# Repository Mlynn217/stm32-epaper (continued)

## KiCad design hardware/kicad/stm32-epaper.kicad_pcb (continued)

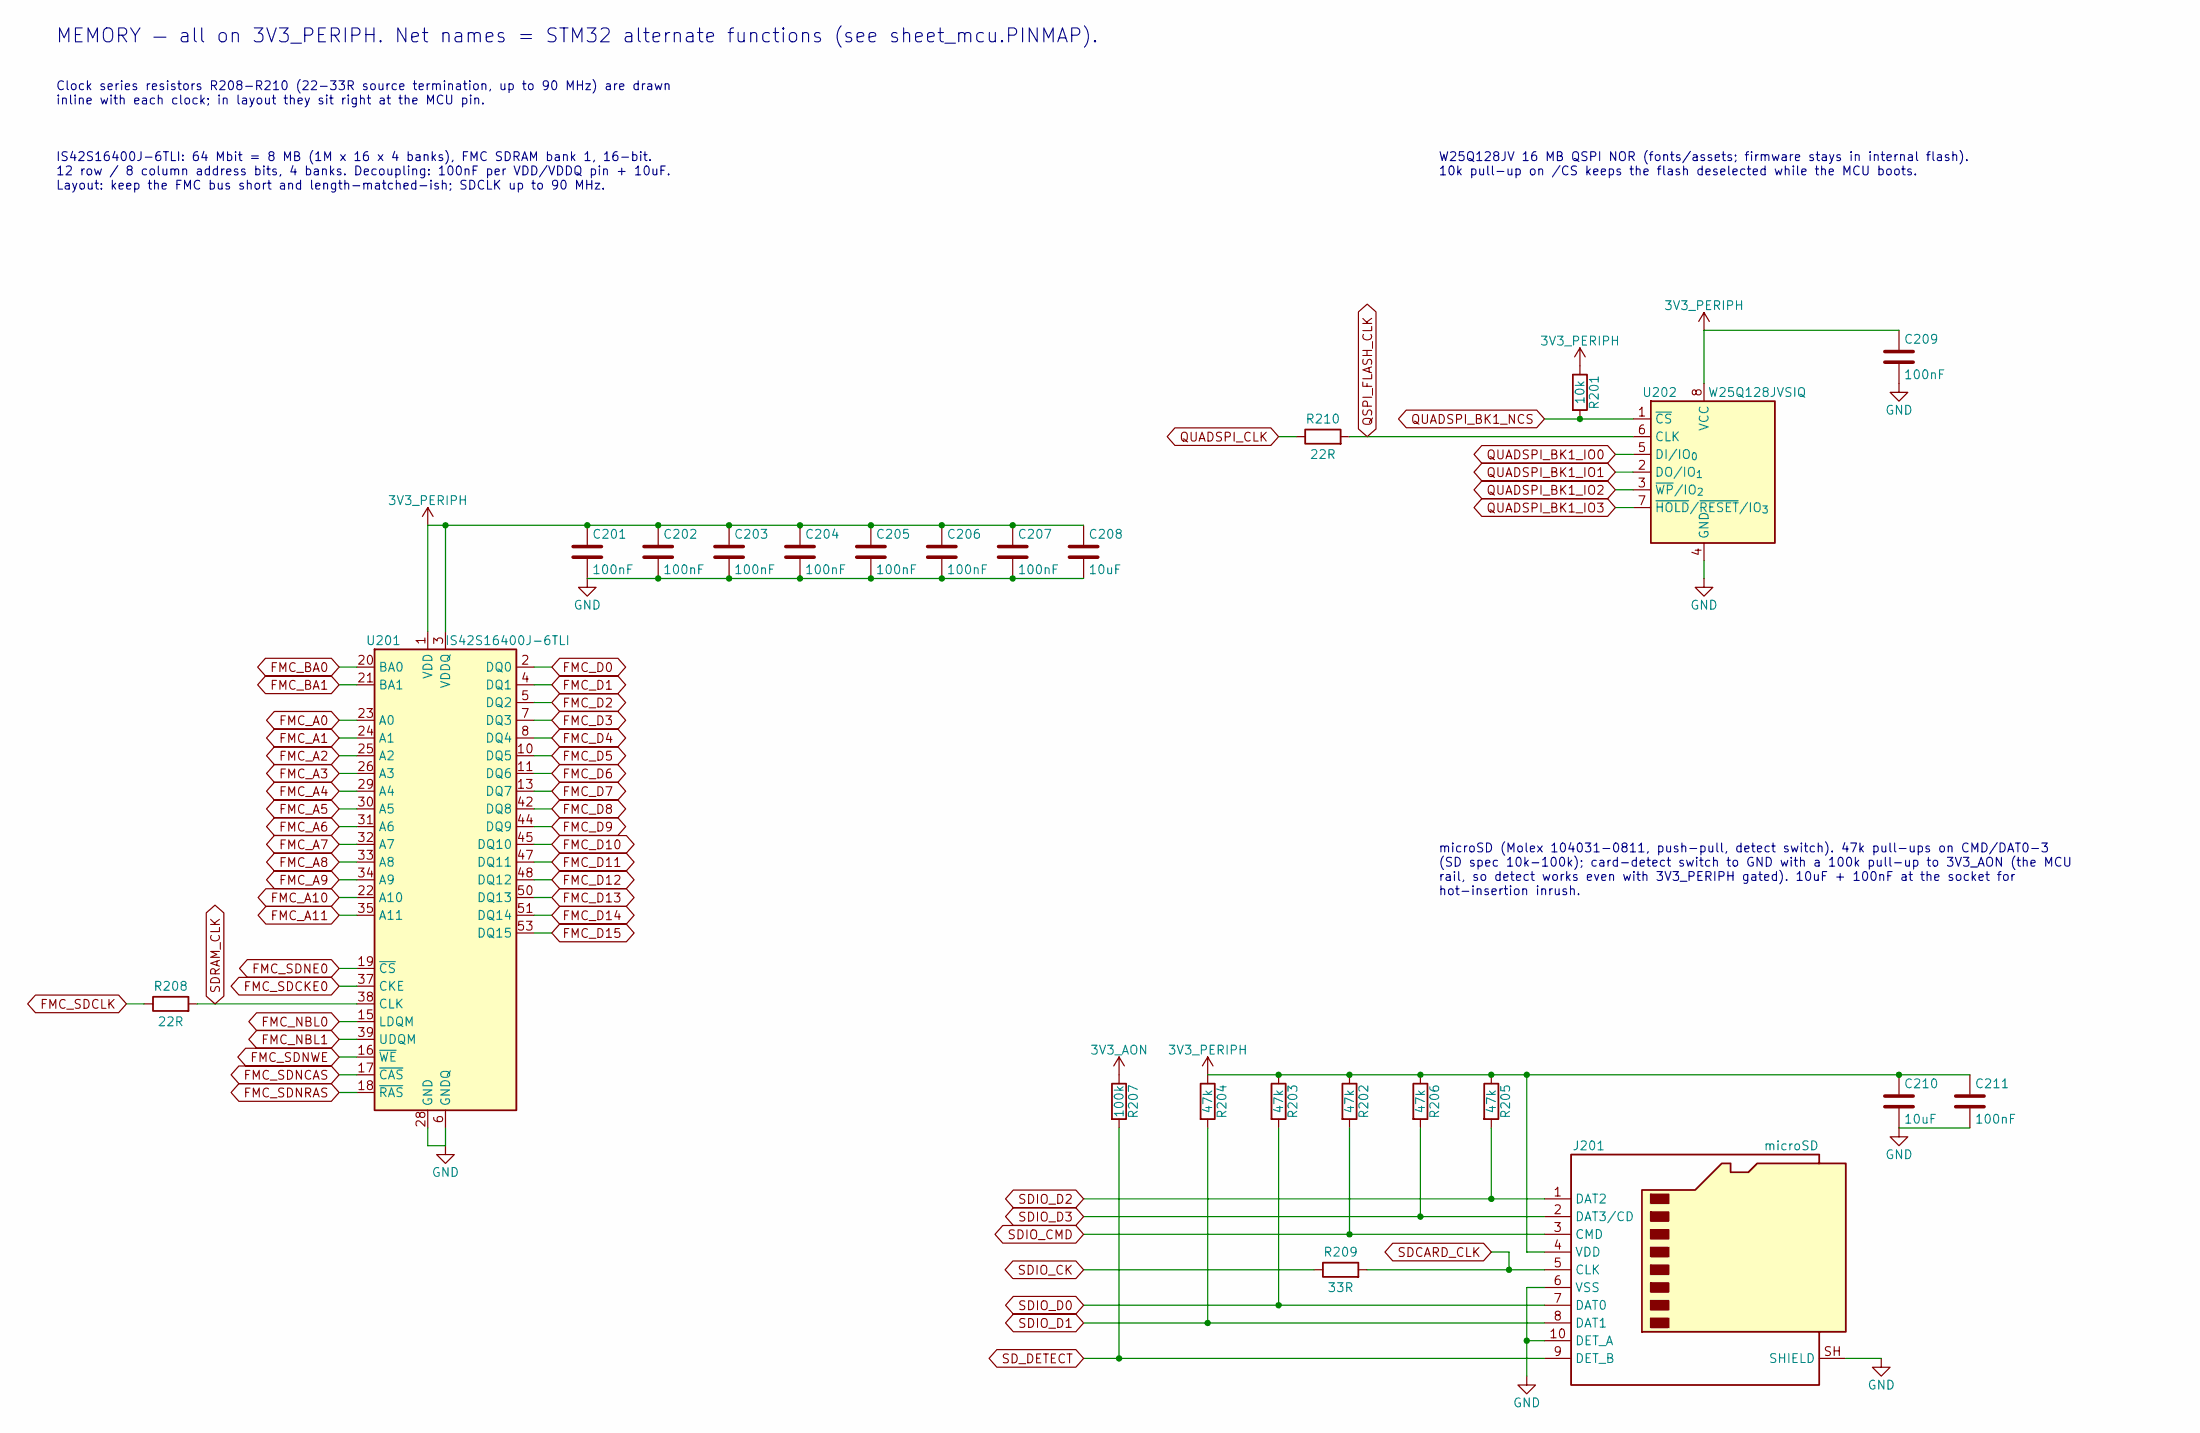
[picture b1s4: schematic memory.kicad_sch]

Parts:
C201, C202, C203, C204, C205, C206, C207, C209, C211: 100nF; C_0402_1005Metric
C208: 10uF; C_0805_2012Metric
C210: 10uF; C_0603_1608Metric
J201: microSD; microSD_HC_Molex_104031-0811; MPN Molex 1040310811
R201: 10k; R_0402_1005Metric
R202, R203, R204, R205, R206: 47k; R_0402_1005Metric
R207: 100k; R_0402_1005Metric
R208, R210: 22R; R_0402_1005Metric
R209: 33R; R_0402_1005Metric
U201: IS42S16400J-6TLI; TSOP-II-54_22.2x10.16mm_P0.8mm; MPN IS42S16400J-6TLI
U202: W25Q128JVSIQ; SOIC-8_5.3x5.3mm_P1.27mm; MPN W25Q128JVSIQ

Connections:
3V3_AON: R207.1; also elsewhere on the board
3V3_PERIPH: C201.1, C202.1, C203.1, C204.1, C205.1, C206.1, C207.1, C208.1, C209.1, C210.1, C211.1, J201.4 (VDD), R201.1, R202.1, R203.1, R204.1, R205.1, R206.1, U201.1 (VDD), U201.3 (VDDQ), U201.9 (VDDQ), U201.14 (VDD), U201.27 (VDD), U201.43 (VDDQ), U201.49 (VDDQ), U202.8 (VCC); also elsewhere on the board
FMC_A0: U201.23 (A0); also elsewhere on the board
FMC_A1: U201.24 (A1); also elsewhere on the board
FMC_A2: U201.25 (A2); also elsewhere on the board
FMC_A3: U201.26 (A3); also elsewhere on the board
FMC_A4: U201.29 (A4); also elsewhere on the board
FMC_A5: U201.30 (A5); also elsewhere on the board
FMC_A6: U201.31 (A6); also elsewhere on the board
FMC_A7: U201.32 (A7); also elsewhere on the board
FMC_A8: U201.33 (A8); also elsewhere on the board
FMC_A9: U201.34 (A9); also elsewhere on the board
FMC_A10: U201.22 (A10); also elsewhere on the board
FMC_A11: U201.35 (A11); also elsewhere on the board
FMC_BA0: U201.20 (BA0); also elsewhere on the board
FMC_BA1: U201.21 (BA1); also elsewhere on the board
FMC_D0: U201.2 (DQ0); also elsewhere on the board
FMC_D1: U201.4 (DQ1); also elsewhere on the board
FMC_D2: U201.5 (DQ2); also elsewhere on the board
FMC_D3: U201.7 (DQ3); also elsewhere on the board
FMC_D4: U201.8 (DQ4); also elsewhere on the board
FMC_D5: U201.10 (DQ5); also elsewhere on the board
FMC_D6: U201.11 (DQ6); also elsewhere on the board
FMC_D7: U201.13 (DQ7); also elsewhere on the board
FMC_D8: U201.42 (DQ8); also elsewhere on the board
FMC_D9: U201.44 (DQ9); also elsewhere on the board
FMC_D10: U201.45 (DQ10); also elsewhere on the board
FMC_D11: U201.47 (DQ11); also elsewhere on the board
FMC_D12: U201.48 (DQ12); also elsewhere on the board
FMC_D13: U201.50 (DQ13); also elsewhere on the board
FMC_D14: U201.51 (DQ14); also elsewhere on the board
FMC_D15: U201.53 (DQ15); also elsewhere on the board
FMC_NBL0: U201.15 (LDQM); also elsewhere on the board
FMC_NBL1: U201.39 (UDQM); also elsewhere on the board
FMC_SDCKE0: U201.37 (CKE); also elsewhere on the board
FMC_SDCLK: R208.1; also elsewhere on the board
FMC_SDNCAS: U201.17 (~CAS); also elsewhere on the board
FMC_SDNE0: U201.19 (~CS); also elsewhere on the board
FMC_SDNRAS: U201.18 (~RAS); also elsewhere on the board
FMC_SDNWE: U201.16 (~WE); also elsewhere on the board
GND: C201.2, C202.2, C203.2, C204.2, C205.2, C206.2, C207.2, C208.2, C209.2, C210.2, C211.2, J201.6 (VSS), J201.10 (DET_A), J201.SH (SHIELD), U201.6 (GNDQ), U201.12 (GNDQ), U201.28 (GND), U201.41 (GND), U201.46 (GNDQ), U201.52 (GNDQ), U201.54 (GND), U202.4 (GND); also elsewhere on the board
QSPI_FLASH_CLK: R210.2, U202.6 (CLK)
QUADSPI_BK1_IO0: U202.5 (DI/IO_{0}); also elsewhere on the board
QUADSPI_BK1_IO1: U202.2 (DO/IO_{1}); also elsewhere on the board
QUADSPI_BK1_IO2: U202.3 (~WP/IO_{2}); also elsewhere on the board
QUADSPI_BK1_IO3: U202.7 (~HOLD/~RESET/IO_{3}); also elsewhere on the board
QUADSPI_BK1_NCS: R201.2, U202.1 (~CS); also elsewhere on the board
QUADSPI_CLK: R210.1; also elsewhere on the board
SDCARD_CLK: J201.5 (CLK), R209.2
SDIO_CK: R209.1; also elsewhere on the board
SDIO_CMD: J201.3 (CMD), R202.2; also elsewhere on the board
SDIO_D0: J201.7 (DAT0), R203.2; also elsewhere on the board
SDIO_D1: J201.8 (DAT1), R204.2; also elsewhere on the board
SDIO_D2: J201.1 (DAT2), R205.2; also elsewhere on the board
SDIO_D3: J201.2 (DAT3/CD), R206.2; also elsewhere on the board
SDRAM_CLK: R208.2, U201.38 (CLK)
SD_DETECT: J201.9 (DET_B), R207.2; also elsewhere on the board

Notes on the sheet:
MEMORY — all on 3V3_PERIPH. Net names = STM32 alternate functions (see sheet_mcu.PINMAP).
Clock series resistors R208-R210 (22-33R source termination, up to 90 MHz) are drawn inline with each clock; in layout they sit right at the MCU pin.
IS42S16400J-6TLI: 64 Mbit = 8 MB (1M x 16 x 4 banks), FMC SDRAM bank 1, 16-bit. 12 row / 8 column address bits, 4 banks. Decoupling: 100nF per VDD/VDDQ pin + 10uF. Layout: keep the FMC bus short and length-matched-ish; SDCLK up to 90 MHz.
W25Q128JV 16 MB QSPI NOR (fonts/assets; firmware stays in internal flash). 10k pull-up on /CS keeps the flash deselected while the MCU boots.
microSD (Molex 104031-0811, push-pull, detect switch). 47k pull-ups on CMD/DAT0-3 (SD spec 10k-100k); card-detect switch to GND with a 100k pull-up to 3V3_AON (the MCU rail, so detect works even with 3V3_PERIPH gated). 10uF + 100nF at the socket for hot-insertion inrush.

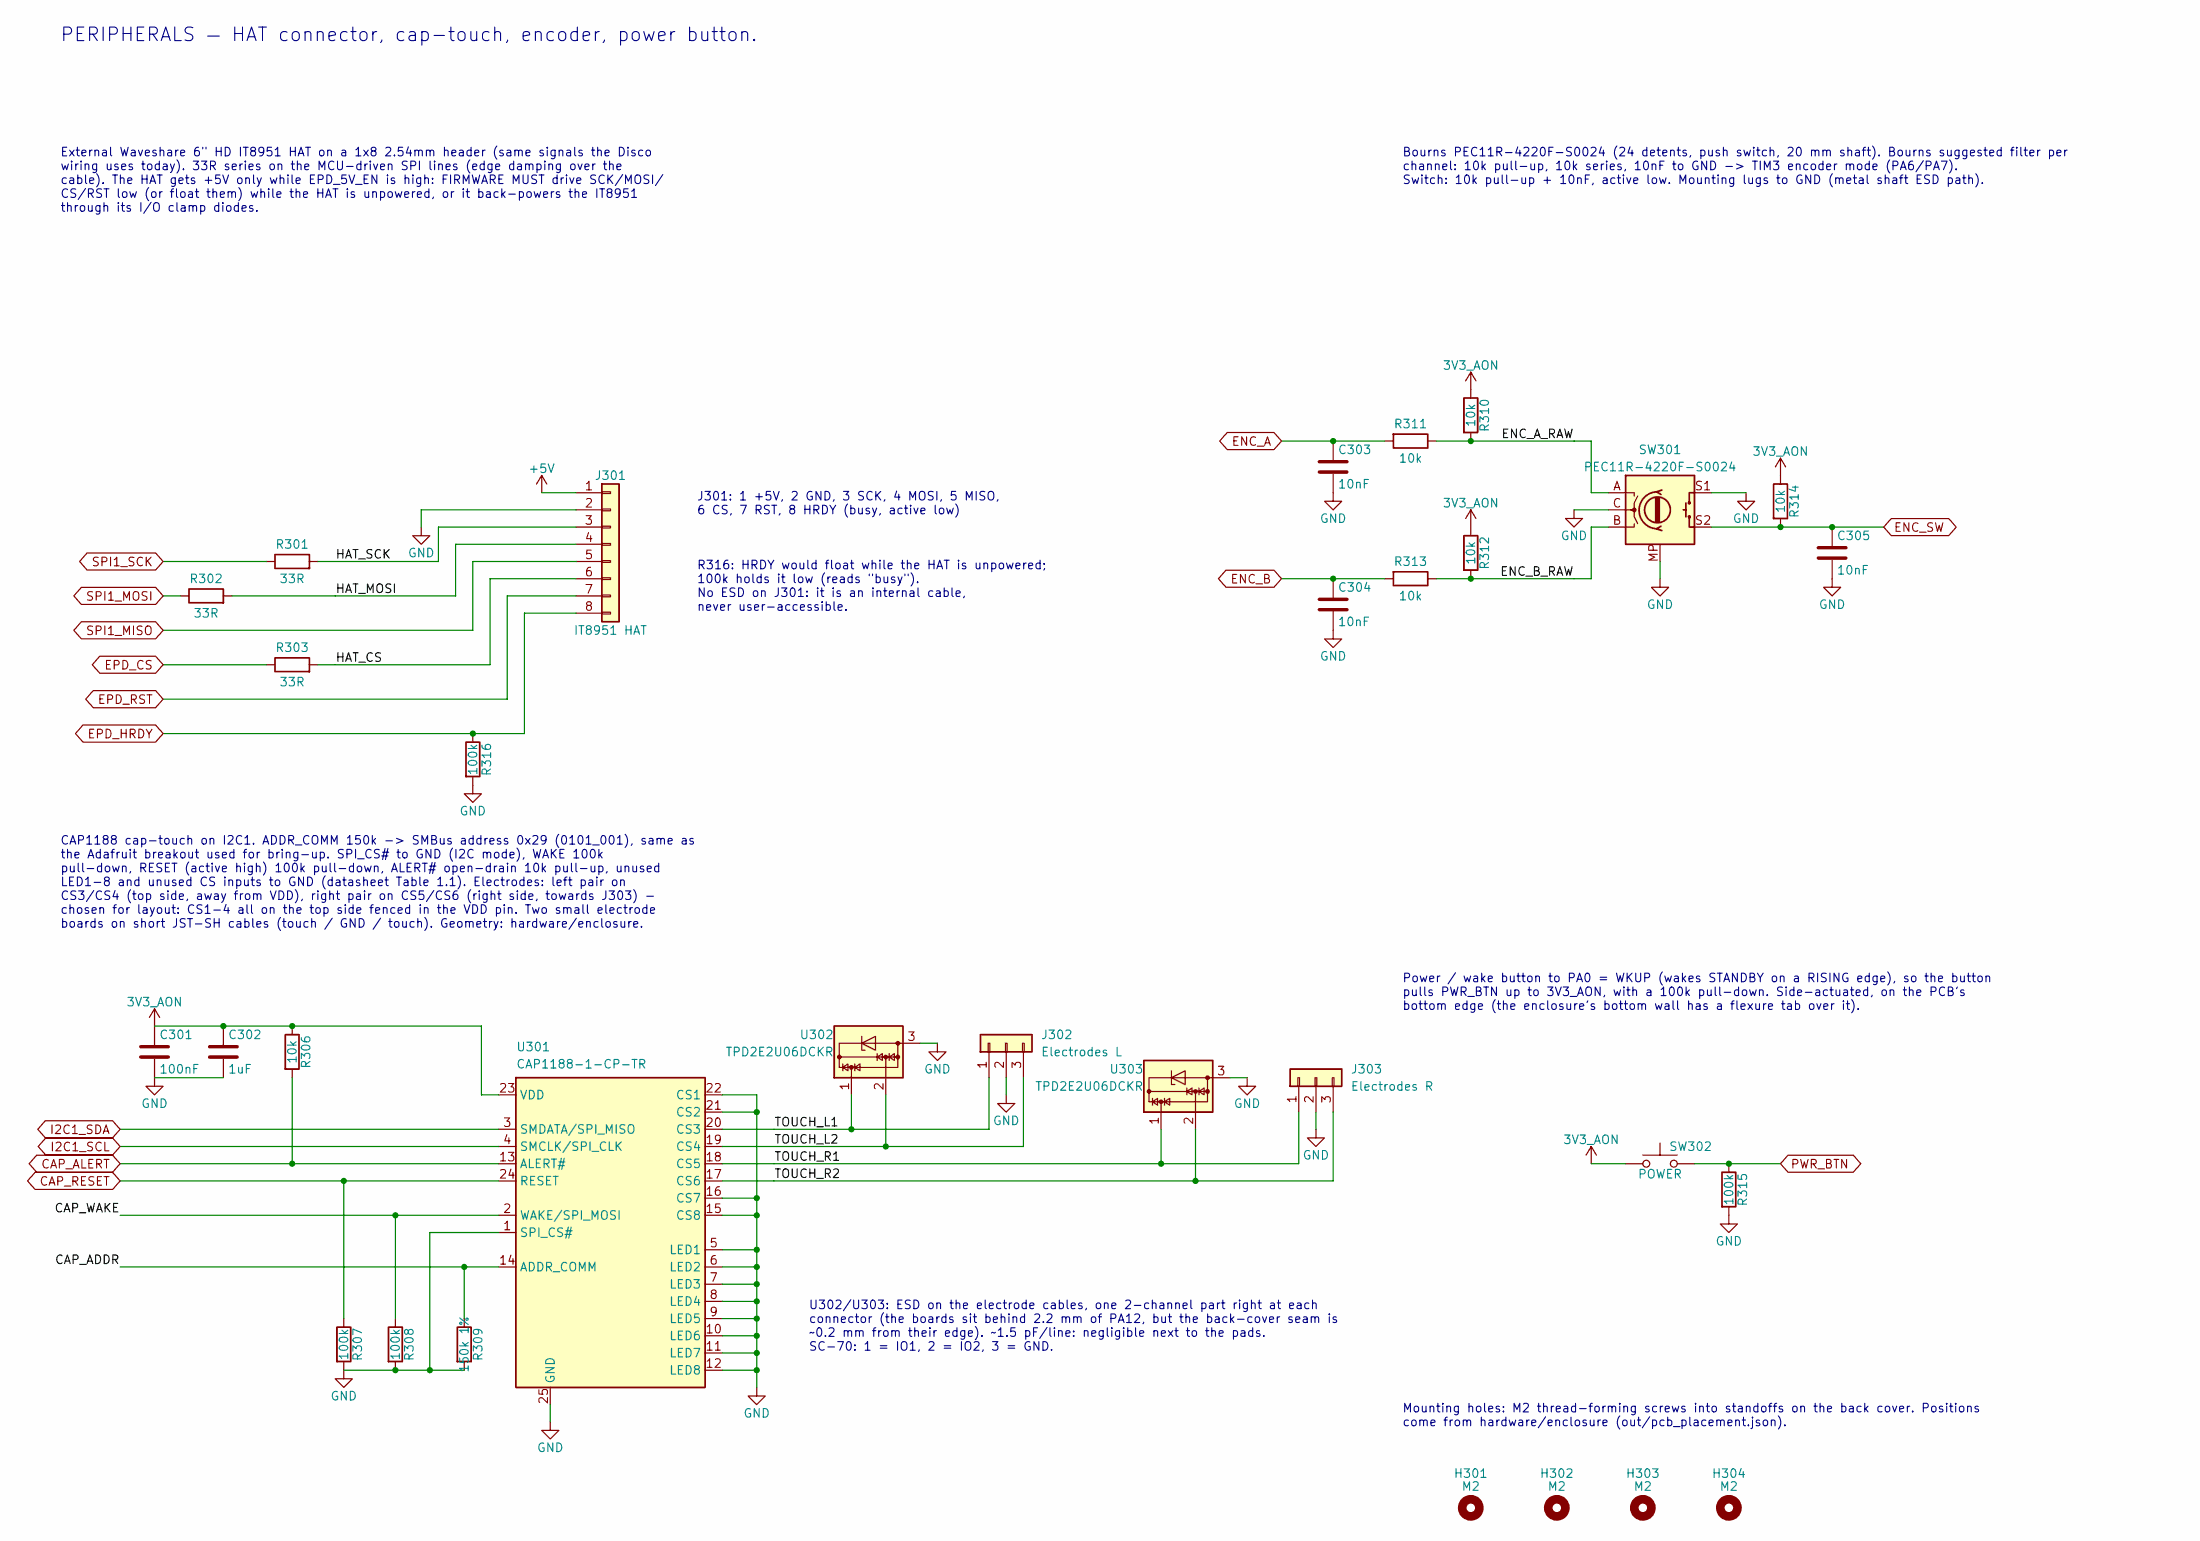
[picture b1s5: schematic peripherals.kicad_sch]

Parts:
C301: 100nF; C_0402_1005Metric
C302: 1uF; C_0402_1005Metric
C303, C304, C305: 10nF; C_0402_1005Metric
H301, H302, H303, H304: M2; MountingHole_2.2mm_M2
J301: IT8951 HAT; PinHeader_1x08_P2.54mm_Vertical
J302: Electrodes L; JST_SH_SM03B-SRSS-TB_1x03-1MP_P1.00mm_Horizontal; MPN SM03B-SRSS-TB
J303: Electrodes R; JST_SH_SM03B-SRSS-TB_1x03-1MP_P1.00mm_Horizontal; MPN SM03B-SRSS-TB
R301, R302, R303: 33R; R_0402_1005Metric
R306, R310, R311, R312, R313, R314: 10k; R_0402_1005Metric
R307, R308, R315, R316: 100k; R_0402_1005Metric
R309: 150k 1%; R_0402_1005Metric
SW301: PEC11R-4220F-S0024; RotaryEncoder_Bourns_Vertical_PEC11R-4xxxF-Sxxxx; MPN PEC11R-4220F-S0024
SW302: POWER; SW_Push_1P1T-MP_NO_Horizontal_Alps_SKRTLAE010; MPN SKRTLAE010
U301: CAP1188-1-CP-TR; QFN-24-1EP_4x4mm_P0.5mm_EP2.5x2.5mm; MPN CAP1188-1-CP-TR
U302, U303: TPD2E2U06DCKR; SOT-323_SC-70; MPN TPD2E2U06DCKR

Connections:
3V3_AON: C301.1, C302.1, R306.1, R310.1, R312.1, R314.1, SW302.1, U301.23 (VDD); also elsewhere on the board
+5V: J301.1; also elsewhere on the board
/Peripherals/CAP_ADDR: R309.1, U301.14 (ADDR_COMM)
/Peripherals/CAP_WAKE: R308.1, U301.2 (WAKE/SPI_MOSI)
/Peripherals/ENC_A_RAW: R310.2, R311.1, SW301.A
/Peripherals/ENC_B_RAW: R312.2, R313.1, SW301.B
/Peripherals/HAT_CS: J301.6, R303.2
/Peripherals/HAT_MOSI: J301.4, R302.2
/Peripherals/HAT_SCK: J301.3, R301.2
/Peripherals/TOUCH_L1: J302.1, U301.20 (CS3), U302.1
/Peripherals/TOUCH_L2: J302.3, U301.19 (CS4), U302.2
/Peripherals/TOUCH_R1: J303.1, U301.18 (CS5), U303.1
/Peripherals/TOUCH_R2: J303.3, U301.17 (CS6), U303.2
CAP_ALERT: R306.2, U301.13 (ALERT#); also elsewhere on the board
CAP_RESET: R307.1, U301.24 (RESET); also elsewhere on the board
ENC_A: C303.1, R311.2; also elsewhere on the board
ENC_B: C304.1, R313.2; also elsewhere on the board
ENC_SW: C305.1, R314.2, SW301.S2; also elsewhere on the board
EPD_CS: R303.1; also elsewhere on the board
EPD_HRDY: J301.8, R316.1; also elsewhere on the board
EPD_RST: J301.7; also elsewhere on the board
GND: C301.2, C302.2, C303.2, C304.2, C305.2, J301.2, J302.2, J303.2, R307.2, R308.2, R309.2, R315.2, R316.2, SW301.C, SW301.MP, SW301.S1, U301.1 (SPI_CS#), U301.5 (LED1), U301.6 (LED2), U301.7 (LED3), U301.8 (LED4), U301.9 (LED5), U301.10 (LED6), U301.11 (LED7), U301.12 (LED8), U301.15 (CS8), U301.16 (CS7), U301.21 (CS2), U301.22 (CS1), U301.25 (GND), U302.3, U303.3; also elsewhere on the board
I2C1_SCL: U301.4 (SMCLK/SPI_CLK); also elsewhere on the board
I2C1_SDA: U301.3 (SMDATA/SPI_MISO); also elsewhere on the board
PWR_BTN: R315.1, SW302.2; also elsewhere on the board
SPI1_MISO: J301.5; also elsewhere on the board
SPI1_MOSI: R302.1; also elsewhere on the board
SPI1_SCK: R301.1; also elsewhere on the board

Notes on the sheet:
PERIPHERALS — HAT connector, cap-touch, encoder, power button.
External Waveshare 6" HD IT8951 HAT on a 1x8 2.54mm header (same signals the Disco wiring uses today). 33R series on the MCU-driven SPI lines (edge damping over the cable). The HAT gets +5V only while EPD_5V_EN is high: FIRMWARE MUST drive SCK/MOSI/ CS/RST low (or float them) while the HAT is unpow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
J301: 1 +5V, 2 GND, 3 SCK, 4 MOSI, 5 MISO, 6 CS, 7 RST, 8 HRDY (busy, active low)
R316: HRDY would float while the HAT is unpowered; 100k holds it low (reads "busy"). No ESD on J301: it is an internal cable, never user-accessible.
CAP1188 cap-touch on I2C1. ADDR_COMM 150k -> SMBus address 0x29 (0101_001), same as the Adafruit breakout used for bring-up. SPI_CS# to GND (I2C mode), WAKE 100k pull-down, RESET (active high) 100k pull-down, ALERT# open-drain 10k pull-up, unused LED1-8 and unused CS inputs to GND (datasheet Table 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
U302/U303: ESD on the electrode cables, one 2-channel part right at each connector (the boards sit behind 2.2 mm of PA12, but the back-cover seam is ~0.2 mm from their edge). ~1.5 pF/line: negligible next to the pads. SC-70: 1 = IO1, 2 = IO2, 3 = GND.
Bourns PEC11R-4220F-S0024 (24 detents, push switch, 20 mm shaft). Bourns suggested filter per channel: 10k pull-up, 10k series, 10nF to GND -> TIM3 encoder mode (PA6/PA7). Switch: 10k pull-up + 10nF, active low. Mounting lugs to GND (metal shaft ESD path).
Power / wake button to PA0 = WKUP (wakes STANDBY on a RISING edge), so the button pulls PWR_BTN up to 3V3_AON, with a 100k pull-down. Side-actuated, on the PCB's bottom edge (the enclosure's bottom wall has a flexure tab over it).
Mounting holes: M2 thread-forming screws into standoffs on the back cover. Positions come from hardware/enclosure (out/pcb_placement.json).

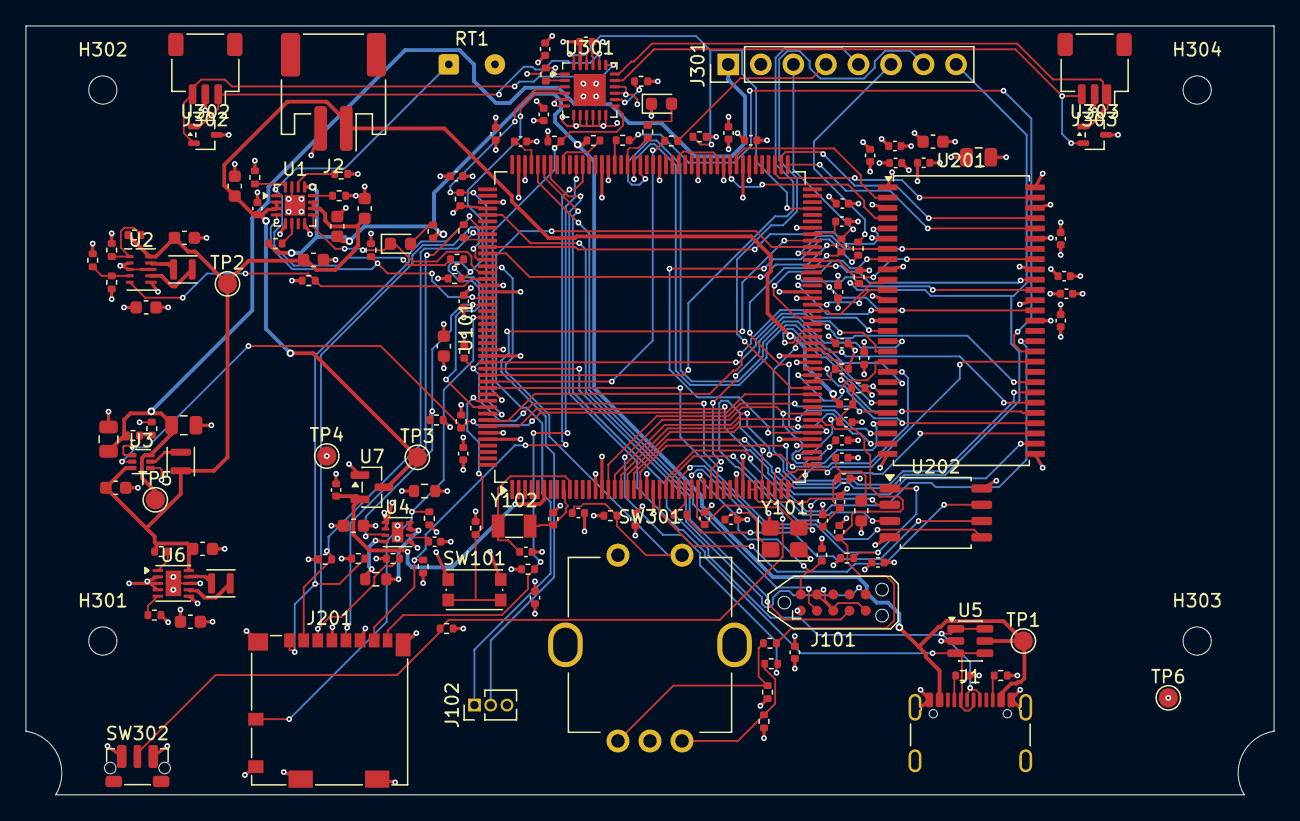
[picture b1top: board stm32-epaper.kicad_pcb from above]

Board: 4 copper layers, 97.4 x 60.0 mm, 156 parts (0 on the bottom side), 135 nets.

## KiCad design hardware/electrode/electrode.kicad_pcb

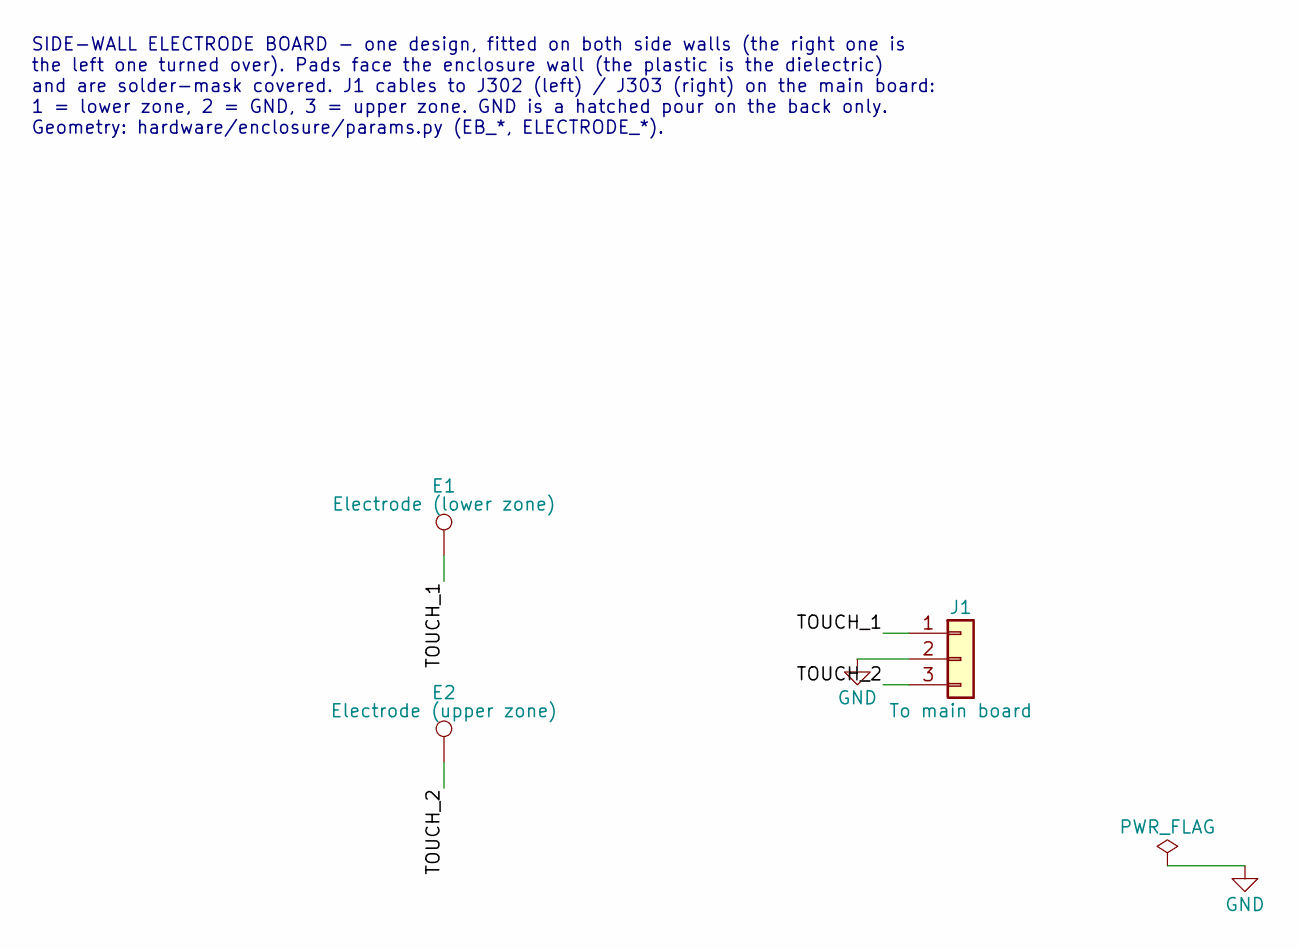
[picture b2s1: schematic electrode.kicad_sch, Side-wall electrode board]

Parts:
E1: Electrode (lower zone); Electrode_Pad_25x8mm
E2: Electrode (upper zone); Electrode_Pad_25x8mm
J1: To main board; JST_SH_SM03B-SRSS-TB_1x03-1MP_P1.00mm_Horizontal; MPN SM03B-SRSS-TB

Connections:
/TOUCH_1: E1.1, J1.1
/TOUCH_2: E2.1, J1.3
GND: J1.2

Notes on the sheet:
SIDE-WALL ELECTRODE BOARD - one design, fitted on both side walls (the right one is the left one turned over). Pads face the enclosure wall (the plastic is the dielectric) and are solder-mask covered. J1 cables to J302 (left) / J303 (right) on the main board: 1 = lower zone, 2 = GND, 3 = upper zone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

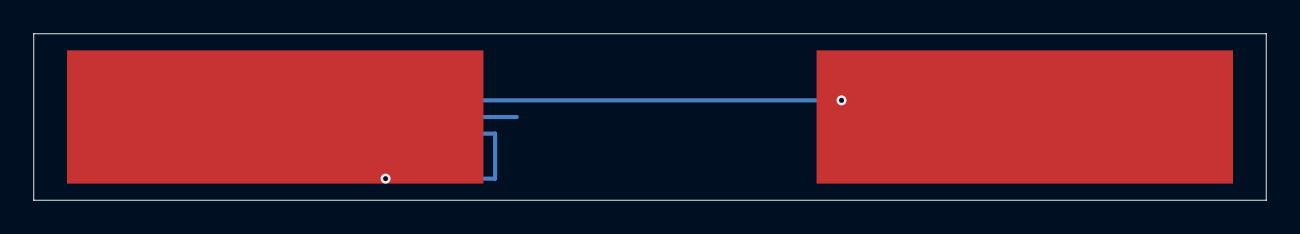
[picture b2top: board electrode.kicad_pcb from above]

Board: 2 copper layers, 74.0 x 10.0 mm, 3 parts (1 on the bottom side), 2 nets.
